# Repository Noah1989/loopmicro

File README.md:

# Loop Microcomputer
a minmal 8-bit machine that is...

- ... independent:
    - contains all the tools required to design another version of itself
    - does not require high soldering skills, uses through-hole parts only
    - uses only "evergreen" parts that have been in production for decades and are still made today

- ... aproachable:
    - simple through reduction
    - NO hidden complexity behind brittle abstractions
    - open source and self-documenting

- ... powerful, with it you can:
    - learn/teach how computers work
    - design electronics
    - control CNC machines / 3d printers
    - play games

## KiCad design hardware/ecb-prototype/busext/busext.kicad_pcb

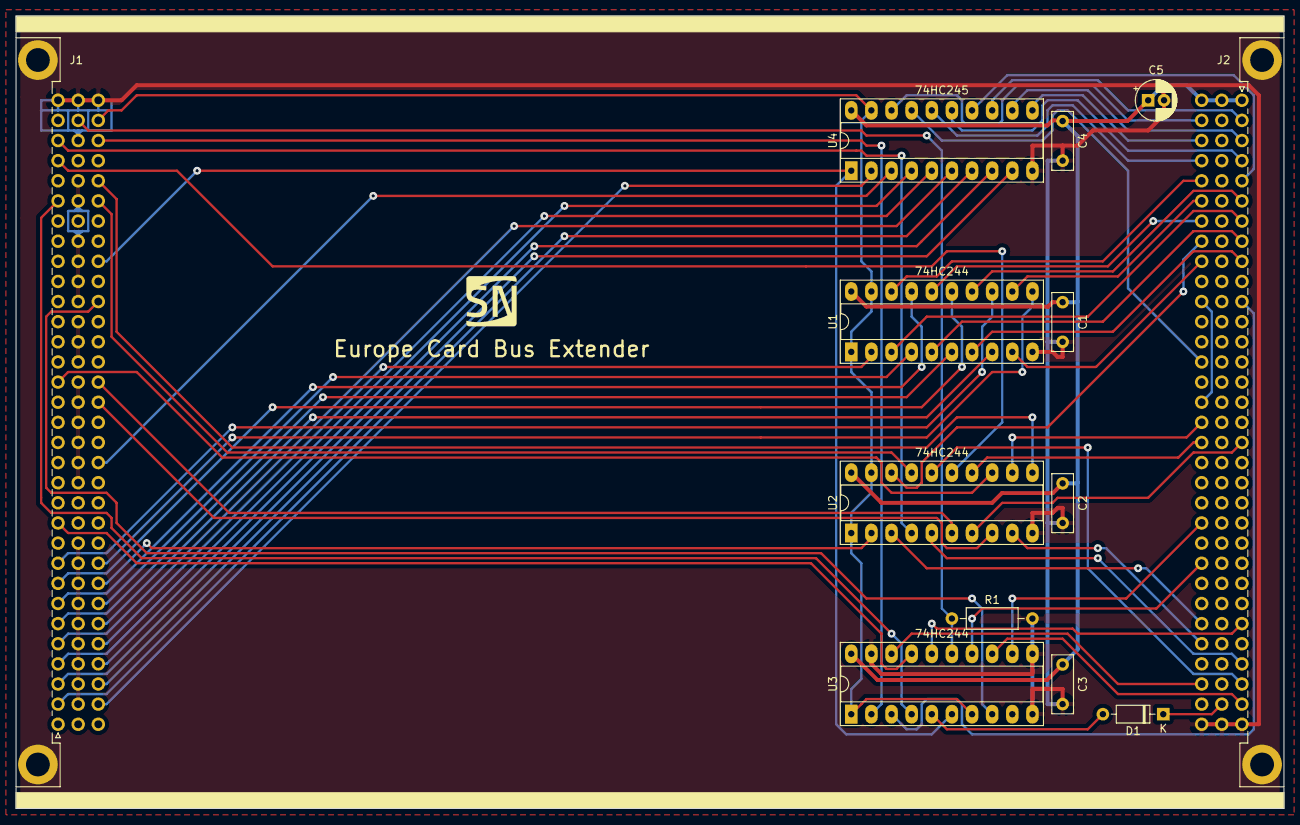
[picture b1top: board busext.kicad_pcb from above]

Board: 2 copper layers, 160.0 x 100.0 mm, 13 parts (0 on the bottom side), 66 nets.

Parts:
C1, C2, C3, C4: 100nF; C_Rect_L7.2mm_W2.5mm_P5.00mm_FKS2_FKP2_MKS2_MKP2
C5: CP; CP_Radial_D5.0mm_P2.00mm
D1: BAT46; D_DO-35_SOD27_P7.62mm_Horizontal
J1, J2: C96ABC; DIN41612_C_3x32_Male_Horizontal_THT
R1: 10k; R_Axial_DIN0207_L6.3mm_D2.5mm_P10.16mm_Horizontal
U1, U2, U3: 74HC244; DIP-20_W7.62mm_Socket_LongPads
U4: 74HC245; DIP-20_W7.62mm_Socket_LongPads

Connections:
GND: C1.1, C2.1, C3.1, C4.1, C5.2, J1.A32, J1.B2, J1.B3, J1.B4, J1.B5, J1.B6, J1.B7, J1.B8, J1.B9, J1.B10, J1.B11, J1.B12, J1.B13, J1.B14, J1.B15, J1.B16, J1.B17, J1.B18, J1.B19, J1.B20, J1.B21, J1.B22, J1.B23, J1.B24, J1.B25, J1.B27, J1.B28, J1.B29, J1.B30, J1.B32, J1.C32, J2.A32, J2.B32, J2.C32, R1.2, U1.10, U2.10, U3.10, U3.11, U3.19, U4.10
MA0: J1.C5, U1.2
MA1: J1.C7, U1.4
MA2: J1.A6, U1.6
MA3: J1.C6, U1.8
MA4: J1.A7, U1.17
MA5: J1.A8, U1.15
MA6: J1.A9, U1.13
MA7: J1.C9, U1.11
MA8: J1.C8, U2.2
MA9: J1.A30, U2.4
MA10: J1.C18, U2.6
MA11: J1.C17, U2.8
MA12: J1.C27, U2.17
MA13: J1.A29, U2.15
MA14: J1.A18, U2.13
MA15: J1.C28, U2.11
MD0: J1.C2, U4.2
MD1: J1.C14, U4.3
MD2: J1.C4, U4.4
MD3: J1.A4, U4.5
MD4: J1.A5, U4.6
MD5: J1.A2, U4.7
MD6: J1.A3, U4.8
MD7: J1.C3, U4.9
MRESB: J1.B31, R1.1, U3.15
unnamed: D1.2, U3.5
unnamed: J2.C11, J2.C16
SA0: J2.C5, U1.18
SA1: J2.C7, U1.16
SA2: J2.A6, U1.14
SA3: J2.C6, U1.12
SA4: J2.A7, U1.3
SA5: J2.A8, U1.5
SA6: J2.A9, U1.7
SA7: J2.C9, U1.9
SA8: J2.C8, U2.18
SA9: J2.A30, U2.16
SA10: J2.C18, U2.14
SA11: J2.C17, U2.12
SA12: J2.C27, U2.3
SA13: J2.A29, U2.5
SA14: J2.A18, U2.7
SA15: J2.C28, U2.9
SD0: J2.C2, U4.18
SD1: J2.C14, U4.17
SD2: J2.C4, U4.16
SD3: J2.A4, U4.15
SD4: J2.A5, U4.14
SD5: J2.A2, U4.13
SD6: J2.A3, U4.12
SD7: J2.C3, U4.11
SRESB: D1.1, J2.B31
VCC: C1.2, C2.2, C3.2, C4.2, C5.1, J2.A1, J2.B1, J2.C1, U1.20, U2.20, U3.20, U4.20
~BUSACK: J1.C31, U1.1, U1.19, U2.1, U2.19, U3.1, U3.7, U4.19
~MBUSRQ: J1.A11, U3.17
~MIORQ: J1.A27, U3.4
~MMREQ: J1.C30, U3.2
~MRD: J1.C24, U3.6, U4.1
~MWR: J1.C22, U3.8
~SBUSACK: J2.A31, U3.13
~SBUSRQ: J2.A11, U3.3
~SIORQ: J2.A27, U3.16
~SMREQ: J2.C30, U3.18
~SRD: J2.C24, U3.14
~SWR: J2.C22, U3.12

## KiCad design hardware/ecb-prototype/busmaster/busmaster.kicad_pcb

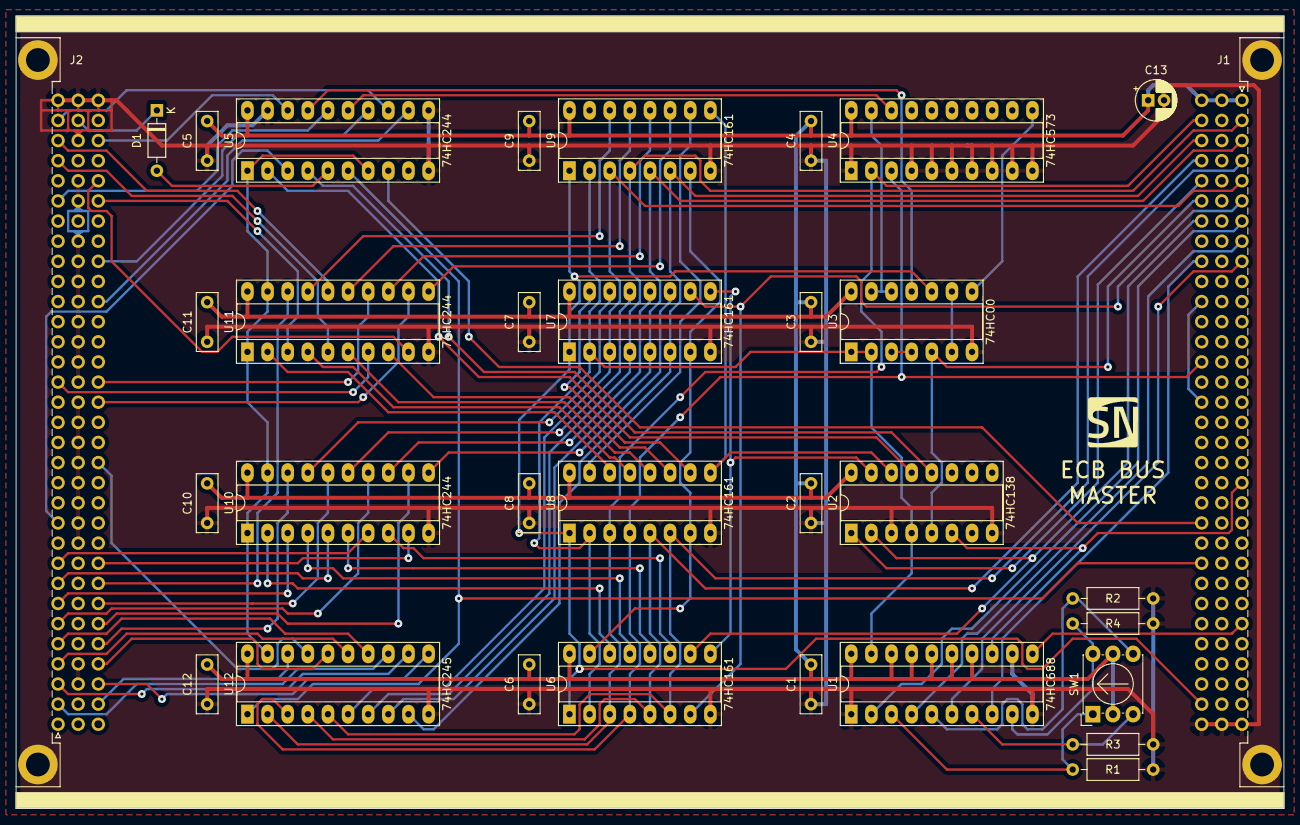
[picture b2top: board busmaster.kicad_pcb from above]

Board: 2 copper layers, 160.0 x 100.0 mm, 33 parts (0 on the bottom side), 91 nets.

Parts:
C1, C2, C3, C4, C5, C6, C7, C8, C9, C10, C11, C12: 100nF; C_Rect_L7.2mm_W2.5mm_P5.00mm_FKS2_FKP2_MKS2_MKP2
C13: CP; CP_Radial_D5.0mm_P2.00mm
D1: BAT46; D_DO-35_SOD27_P7.62mm_Horizontal
J1, J2: C96ABC; DIN41612_C_3x32_Male_Horizontal_THT
R1, R2, R3, R4: R; R_Axial_DIN0207_L6.3mm_D2.5mm_P10.16mm_Horizontal
SW1: SW_Coded_SH-7050; Nidec_Copal_SH-7010C
U1: 74HC688; DIP-20_W7.62mm_Socket_LongPads
U2: 74HC138; DIP-16_W7.62mm_Socket_LongPads
U3: 74HC00; DIP-14_W7.62mm_Socket_LongPads
U4: 74HC573; DIP-20_W7.62mm_Socket_LongPads
U5, U10, U11: 74HC244; DIP-20_W7.62mm_Socket_LongPads
U6, U7, U8, U9: 74HC161; DIP-16_W7.62mm_Socket_LongPads
U12: 74HC245; DIP-20_W7.62mm_Socket_LongPads

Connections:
GND: C1.1, C2.1, C3.1, C4.1, C5.1, C6.1, C7.1, C8.1, C9.1, C10.1, C11.1, C12.1, C13.2, J1.A32, J1.B32, J1.C32, J2.A32, J2.B2, J2.B3, J2.B4, J2.B5, J2.B6, J2.B7, J2.B8, J2.B9, J2.B10, J2.B11, J2.B12, J2.B13, J2.B14, J2.B15, J2.B16, J2.B17, J2.B18, J2.B19, J2.B20, J2.B21, J2.B22, J2.B23, J2.B24, J2.B25, J2.B27, J2.B28, J2.B29, J2.B30, J2.B32, J2.C32, R1.2, R2.2, R3.2, R4.2, U1.1, U1.10, U1.12, U2.3, U2.8, U3.7, U4.1, U4.4, U4.5, U4.6, U4.7, U4.8, U4.9, U4.10, U5.10, U5.11, U5.19, U6.8, U7.8, U8.8, U9.8, U10.10, U11.10, U12.10
MA0: J1.C5, U2.1
MA1: J1.C7, U2.2, U6.10
MA2: J1.A6, U6.7, U7.10
MA3: J1.C6, U2.5, U3.5
MA4: J1.A7, U1.2
MA5: J1.A8, U1.4
MA6: J1.A9, U1.6
MA7: J1.C9, U1.8
MD0: J1.C2, U4.2, U6.3, U8.3, U12.2
MD1: J1.C14, U4.3, U6.4, U8.4, U12.3
MD2: J1.C4, U6.5, U8.5, U12.4
MD3: J1.A4, U6.6, U8.6, U12.5
MD4: J1.A5, U7.3, U9.3, U12.6
MD5: J1.A2, U7.4, U9.4, U12.7
MD6: J1.A3, U7.5, U9.5, U12.8
MD7: J1.C3, U7.6, U9.6, U12.9
unnamed: D1.2, U5.5
unnamed: J1.C11, J1.C16
unnamed: R1.1, SW1.1, U1.3
unnamed: R2.1, SW1.2, U1.5
unnamed: R3.1, SW1.4, U1.7
unnamed: R4.1, SW1.8, U1.9
unnamed: U1.19, U2.4, U3.1, U3.2, U6.2, U7.2, U8.2, U9.2
unnamed: U2.12, U5.4
unnamed: U2.13, U5.2
unnamed: U2.14, U8.9, U9.9
unnamed: U2.15, U6.9, U7.9
unnamed: U3.3, U3.4
unnamed: U3.6, U3.9
unnamed: U3.8, U4.11
unnamed: U3.11, U5.17
unnamed: U3.12, U3.13, U4.19
unnamed: U4.18, U5.15
unnamed: U6.15, U7.7, U8.7, U9.7
unnamed: U7.15, U8.10
unnamed: U8.15, U9.10
unnamed: U6.14, U10.2
unnamed: U6.13, U10.4
unnamed: U6.12, U10.6
unnamed: U6.11, U10.8
unnamed: U7.11, U10.11
unnamed: U7.12, U10.13
unnamed: U7.13, U10.15
unnamed: U7.14, U10.17
unnamed: U8.14, U11.2
unnamed: U8.13, U11.4
unnamed: U8.12, U11.6
unnamed: U8.11, U11.8
unnamed: U9.11, U11.11
unnamed: U9.12, U11.13
unnamed: U9.13, U11.15
unnamed: U9.14, U11.17
SA0: J2.C5, U10.18
SA1: J2.C7, U10.16
SA2: J2.A6, U10.14
SA3: J2.C6, U10.12
SA4: J2.A7, U10.3
SA5: J2.A8, U10.5
SA6: J2.A9, U10.7
SA7: J2.C9, U10.9
SA8: J2.C8, U11.18
SA9: J2.A30, U11.16
SA10: J2.C18, U11.14
SA11: J2.C17, U11.12
SA12: J2.C27, U11.3
SA13: J2.A29, U11.5
SA14: J2.A18, U11.7
SA15: J2.C28, U11.9
SD0: J2.C2, U12.18
SD1: J2.C14, U12.17
SD2: J2.C4, U12.16
SD3: J2.A4, U12.15
SD4: J2.A5, U12.14
SD5: J2.A2, U12.13
SD6: J2.A3, U12.12
SD7: J2.C3, U12.11
SRESB: D1.1, J2.B31
VCC: C1.2, C2.2, C3.2, C4.2, C5.2, C6.2, C7.2, C8.2, C9.2, C10.2, C11.2, C12.2, C13.1, J1.A1, J1.B1, J1.C1, SW1.C, U1.14, U1.15, U1.16, U1.17, U1.18, U1.20, U2.16, U3.14, U4.20, U5.20, U6.16, U7.16, U8.16, U9.16, U10.20, U11.20, U12.20
~BUSACK: U5.1, U5.7, U10.1, U10.19, U11.1, U11.19, U12.19
~MIORQ: J1.A27, U1.11
~MM1: J1.A20, U1.13, U2.6
~MRD: J1.C24, U5.6, U12.1
~MRESET: J1.C31, U3.10, U6.1, U7.1, U8.1, U9.1
~MWR: J1.C22, U5.8
~SBUSACK: J2.A31, U5.13
~SBUSRQ: J2.A11, U5.3
~SIORQ: J2.A27, U5.16
~SMREQ: J2.C30, U5.18
~SRD: J2.C24, U5.14
~SWR: J2.C22, U5.12

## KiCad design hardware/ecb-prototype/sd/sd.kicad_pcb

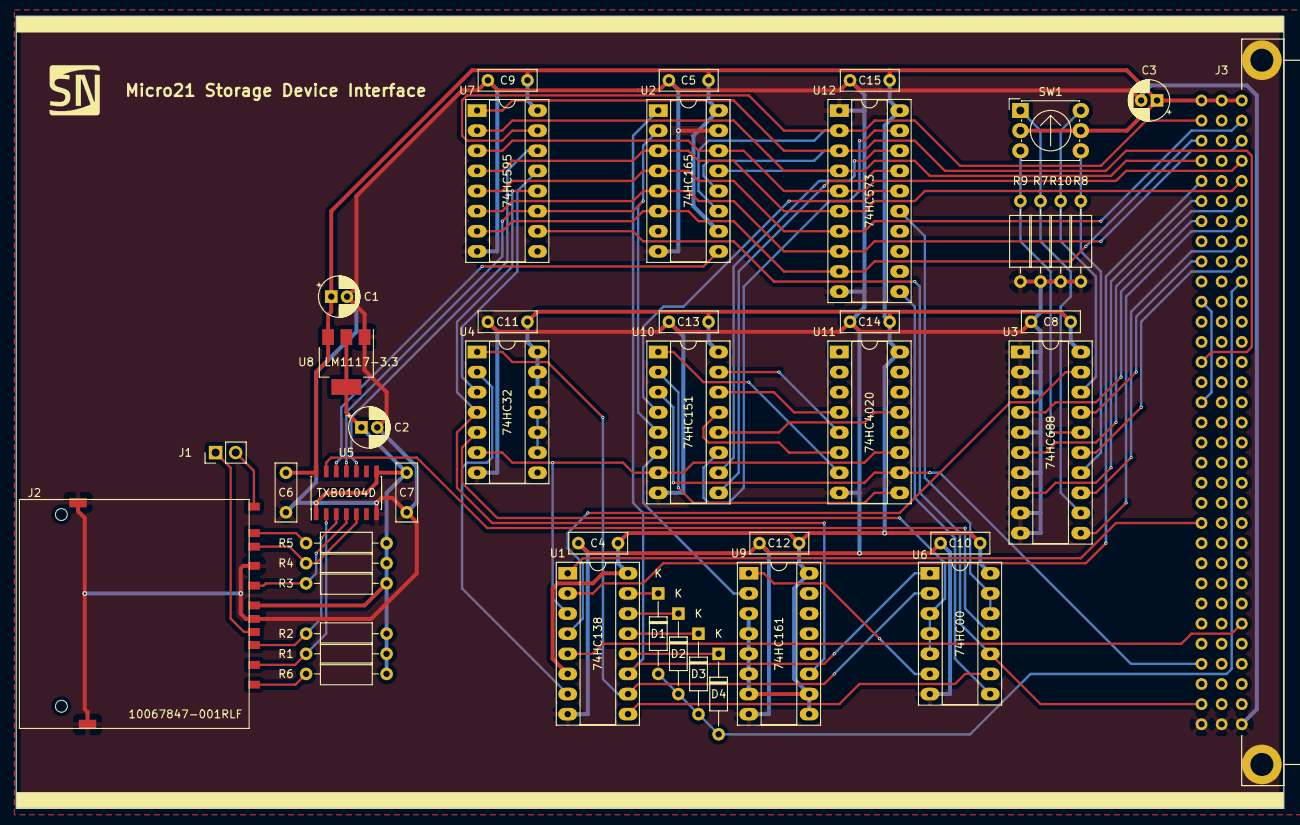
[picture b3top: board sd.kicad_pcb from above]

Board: 2 copper layers, 160.0 x 100.0 mm, 45 parts (0 on the bottom side), 69 nets.

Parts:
C1, C2, C3: CP_Small; CP_Radial_D5.0mm_P2.00mm
C4, C5, C6, C7, C8, C9, C10, C11, C12, C13, C14, C15: C; C_Rect_L7.2mm_W2.5mm_P5.00mm_FKS2_FKP2_MKS2_MKP2
D1, D2, D3, D4: BAT46; D_DO-35_SOD27_P10.16mm_Horizontal
J1: Conn_01x02_Male; PinHeader_1x02_P2.54mm_Vertical
J2: 10067847-001RLF; 10067847
J3: C96ABC; Socket_DIN41612-CaseC1-full-Male-96Pin-3rows
R1, R2, R3, R4, R5, R6, R7, R8, R9, R10: 100k; R_Axial_DIN0207_L6.3mm_D2.5mm_P10.16mm_Horizontal
SW1: SW_Coded_SH-7050; Nidec_Copal_SH-7010C
U1: 74HC138; DIP-16_W7.62mm_Socket_LongPads
U2: 74HC165; DIP-16_W7.62mm_Socket_LongPads
U3: 74HC688; DIP-20_W7.62mm_Socket_LongPads
U4: 74HC32; DIP-14_W7.62mm_Socket_LongPads
U5: TXB0104D; SOIC-14_3.9x8.7mm_P1.27mm
U6: 74HC00; DIP-14_W7.62mm_Socket_LongPads
U7: 74HC595; DIP-16_W7.62mm_Socket_LongPads
U8: LM1117-3.3; SOT-223-3_TabPin2
U9: 74HC161; DIP-16_W7.62mm_Socket_LongPads
U10: 74HC151; DIP-16_W7.62mm_Socket_LongPads
U11: 74HC4020; DIP-16_W7.62mm_Socket_LongPads
U12: 74HC573; DIP-20_W7.62mm_Socket_LongPads

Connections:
+3V3: C2.1, C7.1, J2.4, R1.1, R2.1, R3.1, R4.1, R5.1, R6.1, U5.1, U5.8, U8.2
+5V: C1.1, C3.1, C4.1, C5.1, C6.1, C8.1, C9.1, C10.1, C11.1, C12.1, C13.1, C14.1, C15.1, J3.A1, J3.B1, J3.C1, SW1.C, U1.6, U1.16, U2.10, U2.16, U3.20, U4.12, U4.13, U4.14, U5.14, U6.14, U7.16, U8.3, U9.3, U9.4, U9.5, U9.6, U9.7, U9.9, U9.10, U9.16, U10.16, U11.16, U12.20
/CS: J2.1, R1.2, U5.2
/DI: J2.2, R2.2, U5.3
/DO: J2.7, R4.2, U5.5
/SCLK: J2.5, R3.2, U5.4
A0: J3.C5, U1.2
A1: J3.C7, U3.4
A2: J3.A6, U3.6
A3: J3.C6, U3.8
A4: J3.A7, U3.11
A5: J3.A8, U3.13
A6: J3.A9, U3.15
A7: J3.C9, U3.17
CLK: J3.C29, U10.3, U11.10
D0: J3.C2, U2.11, U7.15, U12.2
D1: J3.C14, U2.12, U7.1, U12.3
D2: J3.C4, U2.13, U7.2, U12.4
D3: J3.A4, U2.14, U7.3, U12.5
D4: J3.A5, U2.3, U7.4, U12.6
D5: J3.A2, U2.4, U7.5, U12.7
D6: J3.A3, U2.5, U7.6, U12.8
D7: J3.C3, U2.6, U7.7, U12.9
GND: C1.2, C2.2, C3.2, C4.2, C5.2, C6.2, C7.2, C8.2, C9.2, C10.2, C11.2, C12.2, C13.2, C14.2, C15.2, J2.3, J2.6, J2.12, J2.13, J3.A32, J3.B32, J3.C32, R7.2, R8.2, R9.2, R10.2, U1.8, U2.8, U2.15, U3.1, U3.2, U3.3, U3.5, U3.7, U3.9, U3.10, U4.7, U5.7, U6.7, U7.8, U8.1, U9.8, U10.8, U11.8, U12.1, U12.10
unnamed: D1.1, U1.15
unnamed: D2.1, U1.14
unnamed: D3.1, U1.13
unnamed: D4.1, U1.12
unnamed: J1.1, J2.10
unnamed: J1.2, J2.11
unnamed: J2.8, R5.2
unnamed: J2.9, R6.2
unnamed: J3.C11, J3.C16
unnamed: R7.1, SW1.1, U3.12
unnamed: R8.1, SW1.2, U3.14
unnamed: R9.1, SW1.4, U3.16
unnamed: R10.1, SW1.8, U3.18
unnamed: U1.3, U4.6, U10.7, U11.11
unnamed: U1.4, U3.19
unnamed: U1.7, U4.2
unnamed: U1.9, U6.9
unnamed: U1.10, U4.1, U6.2
unnamed: U1.11, U2.1, U6.1
unnamed: U2.9, U5.12
unnamed: U4.3, U7.13
unnamed: U4.4, U7.12, U9.11
unnamed: U4.5, U6.3, U6.4, U6.5
unnamed: U4.9, U4.10, U4.11
unnamed: U5.10, U7.14
unnamed: U5.13, U6.11
unnamed: U6.6, U9.1
unnamed: U10.1, U11.7
unnamed: U10.2, U11.9
unnamed: U10.4, U12.16
unnamed: U2.2, U5.11, U7.11, U10.5
unnamed: U9.2, U10.6
unnamed: U10.9, U12.17
unnamed: U10.10, U12.18
unnamed: U10.11, U12.19
unnamed: U10.12, U11.13
unnamed: U10.13, U11.6
unnamed: U10.14, U11.4
unnamed: U10.15, U11.5
unnamed: U6.8, U12.11
unnamed: U6.12, U6.13, U12.15
~IORQ: J3.A27, U1.5
~RESET: J3.C31, U6.10, U7.10
~WAIT: D1.2, D2.2, D3.2, D4.2, J3.A10
~WR: J3.C22, U1.1

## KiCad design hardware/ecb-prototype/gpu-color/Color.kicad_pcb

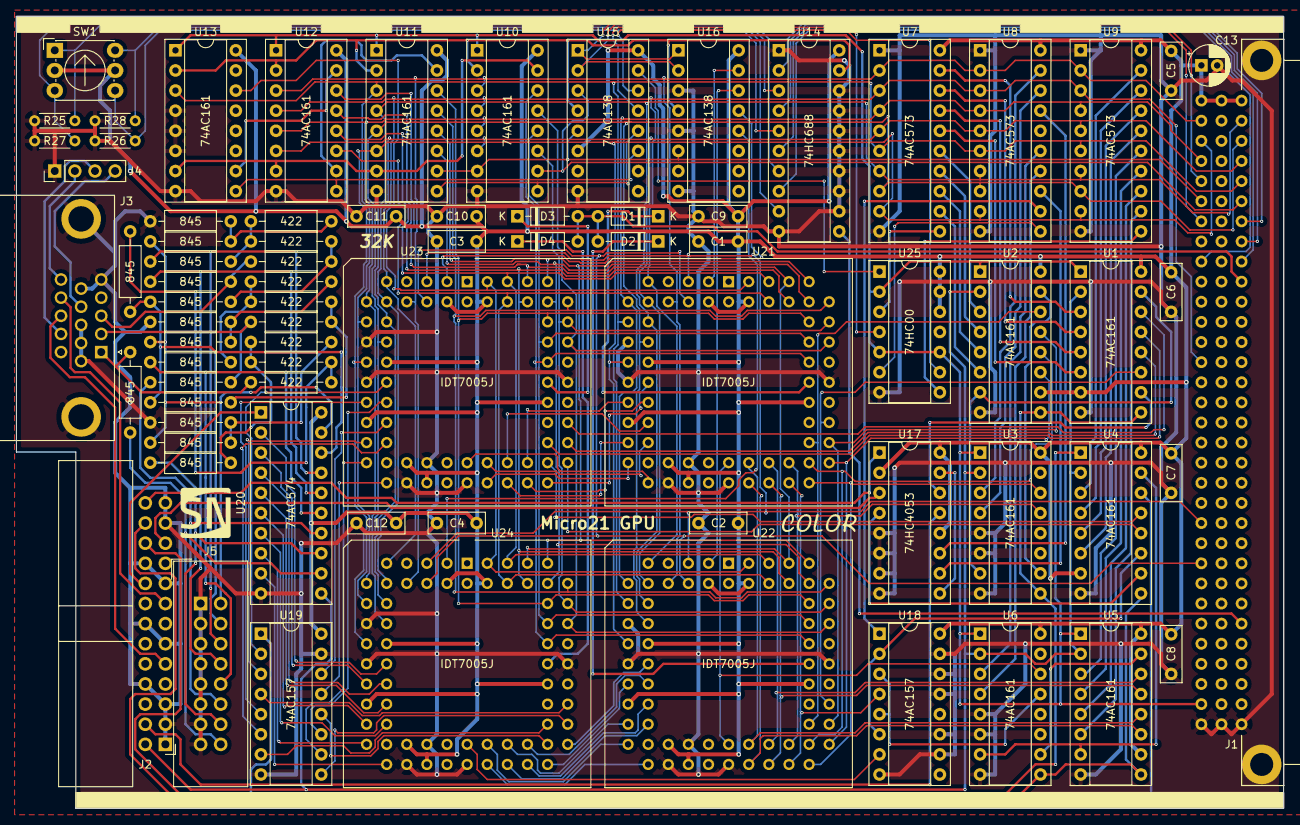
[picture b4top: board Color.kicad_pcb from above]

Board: 2 copper layers, 160.0 x 100.0 mm, 76 parts (0 on the bottom side), 180 nets.

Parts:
C1, C2, C3, C4, C5, C6, C7, C8, C9, C10, C11, C12: C_Small; C_Rect_L7.0mm_W2.5mm_P5.00mm
C13: CP; CP_Radial_D5.0mm_P2.00mm
D1, D2, D3, D4: BAT46; D_DO-35_SOD27_P7.62mm_Horizontal
J1: C96ABC; Socket_DIN41612-CaseC1-full-Male-96Pin-3rows
J2: Conn_01x26_Male; IDC-Header_2x13_P2.54mm_Horizontal
J3: VGA; DSUB-15-HD_Female_Horizontal_P2.29x1.98mm_EdgePinOffset3.03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
J4: I2C; PinHeader_1x04_P2.54mm_Vertical
J5: Conn_02x08_Odd_Even; IDC-Header_2x08_P2.54mm_Vertical
R1, R2, R4, R6, R8, R9, R10, R12, R14, R16, R17, R18, R20, R22, R24: 845; R_Axial_DIN0207_L6.3mm_D2.5mm_P10.16mm_Horizontal
R3, R5, R7, R11, R13, R15, R19, R21, R23: 422; R_Axial_DIN0207_L6.3mm_D2.5mm_P10.16mm_Horizontal
R25, R26, R27, R28: 100k; R_Axial_DIN0204_L3.6mm_D1.6mm_P5.08mm_Horizontal
SW1: SW_Coded_SH-7050; Nidec_Copal_SH-7010C
U1, U2, U3, U4, U5, U6, U10, U11, U12, U13: 74AC161; DIP-16_W7.62mm_Socket
U7, U8, U9: 74AC573; DIP-20_W7.62mm_Socket
U14: 74HC688; DIP-20_W7.62mm_Socket
U15, U16: 74AC138; DIP-16_W7.62mm_Socket
U17: 74HC4053; DIP-16_W7.62mm_Socket
U18, U19: 74AC157; DIP-16_W7.62mm_Socket
U20: 74AC574; DIP-20_W7.62mm_Socket
U21, U22, U23, U24: IDT7005J; PLCC-68_THT-Socket
U25: 74HC00; DIP-14_W7.62mm_Socket

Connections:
/B: J3.3, R7.2, R8.2
/B0: J5.6, R4.1, U20.17
/B1: J5.8, R8.1, U20.16
/Color Table/A0: U1.11, U21.48, U22.48
/Color Table/A1: U2.14, U21.47, U22.47
/Color Table/A2: U2.13, U21.46, U22.46
/Color Table/A3: U2.12, U21.45, U22.45
/Color Table/A4: U2.11, U21.44, U22.44
/Color Table/A5: U3.14, U21.43, U22.43
/Color Table/A6: U3.13, U21.42, U22.42
/Color Table/A7: U18.4, U21.41, U22.41
/Color Table/A8: U5.14, U21.40, U22.40
/Color Table/A9: U5.13, U21.39, U22.39
/Color Table/A10: U5.12, U21.38, U22.38
/Color Table/A11: U5.11, U21.37, U22.37
/Color Table/A12: U6.14, U21.36, U22.36
/Column Counter/CE: U1.10, U17.14
/Column Counter/D0: U1.3, U7.19
/Column Counter/D1: U1.4, U7.18
/Column Counter/D2: U1.5, U7.17
/Column Counter/D3: U1.6, U7.16
/Column Counter/D4: U2.3, U7.15
/Column Counter/D5: U2.4, U7.14
/Column Counter/D6: U2.5, U7.13
/Column Counter/D7: U2.6, U7.12
/Column Counter/D8: U3.3, U8.19
/Column Counter/D9: U3.4, U8.18
/G: J3.2, R15.2, R16.2
/G0: J5.10, R12.1, U20.15
/G1: J5.12, R16.1, U20.14
/I0: J5.2, R2.1, R10.1, R18.1, U20.19
/I1: J5.4, R6.1, R14.1, R22.1, U20.18
/Palette Table/A0: U19.4, U24.48
/Palette Table/A1: U19.7, U24.47
/Palette Table/A2: U19.9, U24.46
/Palette Table/A3: U19.12, U24.45
/Palette Table/A4: U22.19, U24.44
/Palette Table/A5: U22.20, U24.43
/Palette Table/A6: U22.21, U24.42
/Palette Table/A7: U22.23, U24.41
/Palette Table/A8: U22.24, U24.40
/Palette Table/A9: U22.25, U24.39
/Palette Table/A10: U22.26, U24.38
/Palette Table/A11: U22.27, U24.37
/Palette Table/A12: U18.7, U24.36
/Palette Table/Q0: U20.2, U24.19
/Palette Table/Q1: U20.3, U24.20
/Palette Table/Q2: U20.4, U24.21
/Palette Table/Q3: U20.5, U24.23
/Palette Table/Q4: U20.6, U24.24
/Palette Table/Q5: U20.7, U24.25
/Palette Table/Q6: U20.8, U24.26
/Palette Table/Q7: U20.9, U24.27
/Pattern Table/A0: U1.14, U23.48
/Pattern Table/A1: U1.13, U23.47
/Pattern Table/A2: U1.12, U23.46
/Pattern Table/A3: U4.13, U23.45
/Pattern Table/A4: U4.12, U23.44
/Pattern Table/A5: U21.19, U23.43
/Pattern Table/A6: U21.20, U23.42
/Pattern Table/A7: U21.21, U23.41
/Pattern Table/A8: U21.23, U23.40
/Pattern Table/A9: U21.24, U23.39
/Pattern Table/A10: U21.25, U23.38
/Pattern Table/A11: U21.26, U23.37
/Pattern Table/A12: U21.27, U23.36
/Pattern Table/Q0: U19.2, U23.19
/Pattern Table/Q1: U19.5, U23.20
/Pattern Table/Q2: U19.11, U23.21
/Pattern Table/Q3: U19.14, U23.23
/Pattern Table/Q4: U19.3, U23.24
/Pattern Table/Q5: U19.6, U23.25
/Pattern Table/Q6: U19.10, U23.26
/Pattern Table/Q7: U19.13, U23.27
/R: J3.1, R23.2, R24.2
/R0: J5.14, R20.1, U20.13
/R1: J5.16, R24.1, U20.12
/Row Counter/CE: U4.10, U17.4
/Row Counter/D0: U4.3, U9.19
/Row Counter/D1: U4.4, U9.18
/Row Counter/D2: U4.5, U9.17
/Row Counter/D3: U4.6, U9.16
/Row Counter/D4: U5.3, U9.15
/Row Counter/D5: U5.4, U9.14
/Row Counter/D6: U5.5, U9.13
/Row Counter/D7: U5.6, U9.12
/Row Counter/D8: U6.3, U8.15
/Row Counter/D9: U6.4, U8.14
/Row Counter/Q0: U4.14, U19.1
/Row Counter/Q3: U4.11, U18.2, U18.6
/Row Counter/Q9: U6.13, U18.3, U18.5
A0: J1.C5, U15.1, U16.1
A1: J1.C7, U15.2, U16.2
A2: J1.A6, U10.10, U15.3
A3: J1.C6, U10.7, U11.10, U15.5, U16.6
A4: J1.A7, U14.2
A5: J1.A8, U14.4
A6: J1.A9, U14.6
A7: J1.C9, U14.8
AC0: U10.14, U21.55, U22.55, U23.55, U24.55
AC1: U10.13, U21.56, U22.56, U23.56, U24.56
AC2: U10.12, U21.57, U22.57, U23.57, U24.57
AC3: U10.11, U21.58, U22.58, U23.58, U24.58
AC4: U11.14, U21.59, U22.59, U23.59, U24.59
AC5: U11.13, U21.60, U22.60, U23.60, U24.60
AC6: U11.12, U21.61, U22.61, U23.61, U24.61
AC7: U11.11, U21.62, U22.62, U23.62, U24.62
AC8: U12.14, U21.63, U22.63, U23.63, U24.63
AC9: U12.13, U21.64, U22.64, U23.64, U24.64
AC10: U12.12, U21.65, U22.65, U23.65, U24.65
AC11: U12.11, U21.66, U22.66, U23.66, U24.66
AC12: U13.14, U21.67, U22.67, U23.67, U24.67
BLANK: J2.18, U20.1
D0: J1.C2, U7.2, U8.2, U9.2, U10.3, U12.3, U21.8, U22.8, U23.8, U24.8
D1: J1.C14, U7.3, U8.3, U9.3, U10.4, U12.4, U21.9, U22.9, U23.9, U24.9
D2: J1.C4, U7.4, U8.4, U9.4, U10.5, U12.5, U21.10, U22.10, U23.10, U24.10
D3: J1.A4, U7.5, U8.5, U9.5, U10.6, U12.6, U21.11, U22.11, U23.11, U24.11
D4: J1.A5, U7.6, U8.6, U9.6, U11.3, U13.3, U21.12, U22.12, U23.12, U24.12
D5: J1.A2, U7.7, U8.7, U9.7, U11.4, U21.13, U22.13, U23.13, U24.13
D6: J1.A3, U7.8, U8.8, U9.8, U11.5, U21.15, U22.15, U23.15, U24.15
D7: J1.C3, U7.9, U8.9, U9.9, U11.6, U21.16, U22.16, U23.16, U24.16
GND: C1.1, C2.1, C3.1, C4.1, C5.1, C6.1, C7.1, C8.1, C9.1, C10.1, C11.1, C12.1, C13.2, J1.A32, J1.B32, J1.C32, J2.1, J2.3, J2.5, J2.8, J2.11, J2.14, J2.17, J2.20, J2.23, J2.25, J3.0, J3.5, J3.6, J3.7, J3.8, J3.10, J4.1, J5.1, J5.3, J5.5, J5.7, J5.9, J5.11, J5.13, J5.15, R1.1, R9.1, R17.1, R25.2, R26.2, R27.2, R28.2, U1.8, U2.8, U3.5, U3.6, U3.8, U4.8, U5.8, U6.5, U6.6, U6.8, U7.1, U7.10, U8.1, U8.10, U9.1, U9.10, U10.8, U11.8, U12.8, U13.4, U13.5, U13.6, U13.8, U14.1, U14.10, U14.12, U14.13, U14.14, U14.15, U14.16, U14.17, U14.18, U15.8, U16.3, U16.5, U16.8, U17.5, U17.6, U17.7, U17.8, U18.8, U18.10, U18.11, U18.13, U18.14, U18.15, U19.8, U19.15, U20.10, U21.14, U21.18, U21.29, U21.32, U21.35, U21.52, U22.14, U22.18, U22.29, U22.32, U22.35, U22.52, U23.14, U23.18, U23.29, U23.32, U23.35, U23.52, U24.14, U24.18, U24.29, U24.32, U24.35, U24.52, U25.7
HSYNC: J2.9, J3.13
unnamed: D1.1, U21.53
unnamed: D2.1, U22.53
unnamed: D3.1, U23.53
unnamed: D4.1, U24.53
unnamed: J3.9, J4.4
unnamed: R1.2, R2.2, R3.1
unnamed: R3.2, R4.2, R5.1
unnamed: R5.2, R6.2, R7.1
unnamed: R9.2, R10.2, R11.1
unnamed: R11.2, R12.2, R13.1
unnamed: R13.2, R14.2, R15.1
unnamed: R17.2, R18.2, R19.1
unnamed: R19.2, R20.2, R21.1
unnamed: R21.2, R22.2, R23.1
unnamed: R25.1, SW1.1, U14.3
unnamed: R26.1, SW1.2, U14.5
unnamed: R27.1, SW1.4, U14.7
unnamed: R28.1, SW1.8, U14.9
unnamed: U1.15, U2.7, U3.7
unnamed: U2.15, U3.10
unnamed: U4.15, U5.7, U6.7
unnamed: U5.15, U6.10
unnamed: U10.2, U11.2, U12.2, U13.2, U14.19, U15.4, U16.4
unnamed: U10.15, U11.7, U12.7, U13.7
unnamed: U11.15, U12.10
unnamed: U12.15, U13.10
unnamed: U8.13, U17.10
unnamed: U8.17, U17.11
unnamed: U17.9, U17.15
unnamed: U8.12, U18.1
unnamed: U7.11, U25.3
unnamed: U8.11, U25.6
unnamed: U9.11, U25.8
ODDCOL: J2.4, U17.13
ODDROW: J2.26, U17.1
PCLK: J2.2, U1.2, U2.2, U3.2, U4.2, U5.2, U6.2, U20.11
SCL: J3.15, J4.2
SDA: J3.12, J4.3
TCC: J2.21, U17.3
VCC: C1.2, C2.2, C3.2, C4.2, C5.2, C6.2, C7.2, C8.2, C9.2, C10.2, C11.2, C12.2, C13.1, J1.A1, J1.B1, J1.C1, SW1.C, U1.7, U1.16, U2.10, U2.16, U3.16, U4.7, U4.16, U5.10, U5.16, U6.16, U7.20, U8.20, U9.20, U10.16, U11.16, U12.16, U13.16, U14.20, U15.6, U15.16, U16.16, U17.2, U17.12, U17.16, U18.16, U19.16, U20.20, U21.4, U21.17, U21.22, U21.30, U21.31, U21.51, U21.68, U22.4, U22.17, U22.22, U22.30, U22.31, U22.51, U22.68, U23.4, U23.17, U23.22, U23.30, U23.31, U23.51, U23.68, U24.4, U24.17, U24.22, U24.30, U24.31, U24.51, U24.68, U25.12, U25.13, U25.14
VSYNC: J2.15, J3.14
~CS0: U15.15, U25.1
~CS1: U15.14, U25.9
~CS2: U15.13, U25.4
~CS3: U10.9, U11.9, U15.12
~CS4: U12.9, U13.9, U15.11
~CS8: U16.15, U21.3
~CS9: U16.14, U22.3
~CS10: U16.13, U23.3
~CS11: U16.12, U24.3
~IORQ: J1.A27, U14.11
~RD: J1.C24, U21.6, U22.6, U23.6, U24.6
~RESET: J1.C31, U1.1, U2.1, U3.1, U4.1, U5.1, U6.1, U10.1, U11.1, U12.1, U13.1, U25.2, U25.5, U25.10
~TCC: J2.22, U1.9, U2.9, U3.9
~TCR: J2.24, U4.9, U5.9, U6.9
~WAIT: D1.2, D2.2, D3.2, D4.2, J1.A10
~WR: J1.C22, U21.5, U22.5, U23.5, U24.5

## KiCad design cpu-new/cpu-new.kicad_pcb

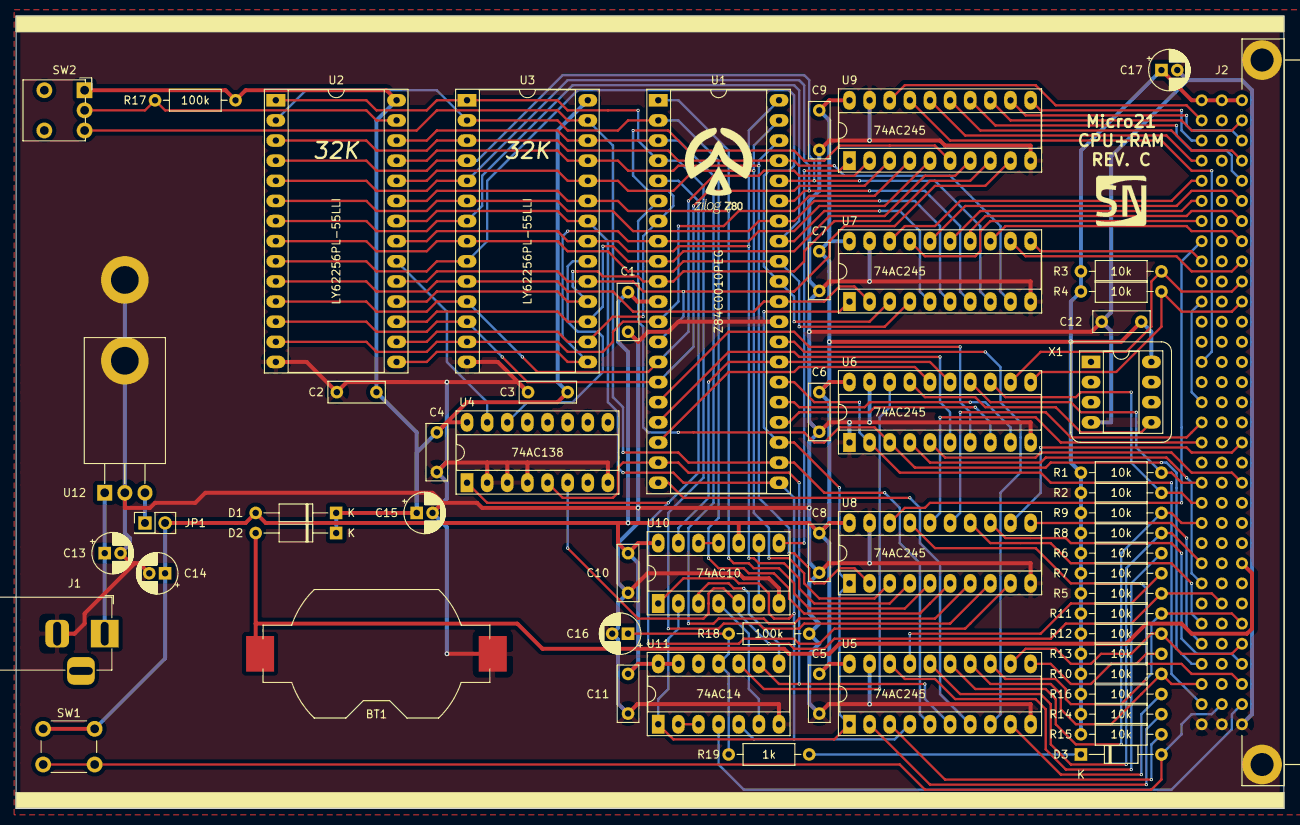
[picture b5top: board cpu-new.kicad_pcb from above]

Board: 2 copper layers, 160.0 x 100.0 mm, 58 parts (0 on the bottom side), 102 nets.

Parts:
BT1: CR2032; BatteryHolder_Keystone_1058_1x2032
C1, C2, C3, C4, C5, C6, C7, C8, C9, C10, C11, C12: 100nF; C_Rect_L7.0mm_W2.5mm_P5.00mm
C13, C14: 10µF; CP_Radial_D5.0mm_P2.00mm
C15, C16, C17: 1µF; CP_Radial_D5.0mm_P2.00mm
D1, D2, D3: BAT46; D_DO-35_SOD27_P10.16mm_Horizontal
J1: Barrel_Jack; BarrelJack_Horizontal
J2: C96ABC; Socket_DIN41612-CaseC1-full-Male-96Pin-3rows
JP1: Jumper; PinHeader_2x01_P2.54mm_Vertical
R1, R2, R3, R4, R5, R6, R7, R8, R9, R10, R11, R12, R13, R14, R15, R16: 10k; R_Axial_DIN0207_L6.3mm_D2.5mm_P10.16mm_Horizontal
R17, R18: 100k; R_Axial_DIN0207_L6.3mm_D2.5mm_P10.16mm_Horizontal
R19: 1k; R_Axial_DIN0207_L6.3mm_D2.5mm_P10.16mm_Horizontal
SW1: SW_Push; SW_PUSH_6mm_H5mm
SW2: SW_SPDT; SW_Lever_1P2T_NKK_GW12LxH
U1: Z84C0010PEG; DIP-40_W15.24mm_Socket_LongPads
U2, U3: LY62256PL-55LLI; DIP-28_W15.24mm_Socket_LongPads
U4: 74AC138; DIP-16_W7.62mm_Socket_LongPads
U5, U6, U7, U8, U9: 74AC245; DIP-20_W7.62mm_Socket_LongPads
U10: 74AC10; DIP-14_W7.62mm_Socket_LongPads
U11: 74AC14; DIP-14_W7.62mm_Socket_LongPads
U12: L7805; TO-220-3_Horizontal_TabDown
X1: 10MHz; DIP-8_W7.62mm_Socket_LongPads

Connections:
+BATT: BT1.1, D2.2, J2.A24
A0: J2.C5, U7.18
A1: J2.C7, U7.17
A2: J2.A6, U7.16
A3: J2.C6, U7.15
A4: J2.A7, U7.14
A5: J2.A8, U7.13
A6: J2.A9, U7.12
A7: J2.C9, U7.11
A8: J2.C8, U8.18
A9: J2.A30, U8.17
A10: J2.C18, U8.16
A11: J2.C17, U8.15
A12: J2.C27, U8.14
A13: J2.A29, U8.13
A14: J2.A18, U8.12
A15: J2.C28, U8.11
CLK: J2.C29, U1.6, U6.3
D0: J2.C2, U9.18
D1: J2.C14, U9.17
D2: J2.C4, U9.16
D3: J2.A4, U9.15
D4: J2.A5, U9.14
D5: J2.A2, U9.13
D6: J2.A3, U9.12
D7: J2.C3, U9.11
GND: BT1.2, C1.2, C2.2, C3.2, C4.2, C5.2, C6.2, C7.2, C8.2, C9.2, C10.2, C11.2, C12.1, C13.2, C14.2, C15.2, C16.2, C17.2, J1.2, J2.A32, J2.B32, J2.C32, R18.1, U1.29, U2.14, U3.14, U4.2, U4.3, U4.4, U4.8, U5.10, U5.19, U6.1, U6.10, U6.19, U7.10, U7.19, U8.10, U8.19, U9.10, U9.19, U10.7, U11.7, U12.2, X1.4
unnamed: C13.1, J1.1, U12.1
unnamed: C16.1, R18.2, R19.2, U11.11
unnamed: D3.1, R19.1
unnamed: J2.C11, J2.C16
unnamed: JP1.1, U12.3
unnamed: R6.1, U5.18
unnamed: R7.1, U5.17
unnamed: R13.1, U5.11
unnamed: R14.1, U5.2
unnamed: R15.1, U5.3
unnamed: R16.1, U5.9
unnamed: R17.2, SW2.2, U2.27
unnamed: SW2.3, U1.22, U3.27, U5.5
unnamed: U1.1, U2.23, U3.23, U8.5
unnamed: U1.2, U2.2, U3.2, U8.6
unnamed: U1.3, U2.26, U3.26, U8.7
unnamed: U1.4, U2.1, U3.1, U8.8
unnamed: U1.5, U4.1, U8.9
unnamed: U1.7, U2.16, U3.16, U9.6
unnamed: U1.8, U2.15, U3.15, U9.5
unnamed: U1.9, U2.17, U3.17, U9.7
unnamed: U1.10, U2.18, U3.18, U9.8
unnamed: U1.12, U2.13, U3.13, U9.4
unnamed: U1.13, U2.19, U3.19, U9.9
unnamed: U1.14, U2.11, U3.11, U9.2
unnamed: U1.15, U2.12, U3.12, U9.3
unnamed: U1.16, U6.7
unnamed: U1.17, U6.6
unnamed: U1.18, U6.16
unnamed: U1.19, U4.5, U5.6, U11.9
unnamed: U1.20, U5.7
unnamed: U1.21, U2.22, U3.22, U5.4, U10.1, U11.5
unnamed: U1.23, U5.1, U7.1, U8.1, U10.2, U11.1
unnamed: U1.24, U6.8
unnamed: U1.25, U6.9
unnamed: U1.27, U6.15, U10.13
unnamed: U1.28, U5.8
unnamed: U1.30, U2.10, U3.10, U7.2
unnamed: U1.31, U2.9, U3.9, U7.3
unnamed: U1.32, U2.8, U3.8, U7.4
unnamed: U1.33, U2.7, U3.7, U7.5
unnamed: U1.34, U2.6, U3.6, U7.6
unnamed: U1.35, U2.5, U3.5, U7.7
unnamed: U1.36, U2.4, U3.4, U7.8
unnamed: U1.37, U2.3, U3.3, U7.9
unnamed: U1.38, U2.25, U3.25, U8.2
unnamed: U1.39, U2.24, U3.24, U8.3
unnamed: U1.40, U2.21, U3.21, U8.4
unnamed: U2.20, U4.15
unnamed: U3.20, U4.14
unnamed: U6.17, X1.5
unnamed: U10.3, U11.8
unnamed: U10.4, U11.6
unnamed: U10.6, U10.9
unnamed: U9.1, U10.8
unnamed: U10.11, U10.12
unnamed: U11.2, U11.3
unnamed: U6.18, U11.10
RESB: D3.2, J2.B31, SW1.2
VCC: C1.1, C5.1, C6.1, C7.1, C8.1, C9.1, C10.1, C11.1, C12.2, C14.1, C17.1, D1.2, J2.A1, J2.B1, J2.C1, JP1.2, R1.2, R2.2, R3.2, R4.2, R5.2, R6.2, R7.2, R8.2, R9.2, R10.2, R11.2, R12.2, R13.2, R14.2, R15.2, R16.2, SW1.1, U1.11, U5.20, U6.20, U7.20, U8.20, U9.20, U10.10, U10.14, U11.13, U11.14, X1.8
VMEM: C2.1, C3.1, C4.1, C15.1, D1.1, D2.1, R17.1, SW2.1, U2.28, U3.28, U4.16
~BUSACK: J2.A31, U11.4
~BUSRQ: J2.A11, R4.1, U6.11
~EXM: J2.B26, R5.1, U4.6, U10.5
~HALT: J2.C25, U6.4
~INT: J2.C21, R2.1, U6.13
~IORQ: J2.A27, R11.1, U5.13
~M1: J2.A20, U6.5
~MREQ: J2.C30, R10.1, U5.14
~NMI: J2.C20, R1.1, U6.14
~RD: J2.C24, R8.1, U5.16
~RESET: J2.C31, U1.26, U6.2
~RFSH: J2.A28, R12.1, U5.12
~WAIT: J2.A10, R3.1, U6.12
~WR: J2.C22, R9.1, U5.15
